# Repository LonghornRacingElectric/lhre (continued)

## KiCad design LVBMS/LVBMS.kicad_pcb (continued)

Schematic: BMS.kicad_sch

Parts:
C26, C27: 10n; C_0603_1608Metric_Pad1.08x0.95mm_HandSolder; Mouser # 581-KAM05AR71E103KH; JLCPCB # C1589
C28, C29, C30: 1u; C_0603_1608Metric_Pad1.08x0.95mm_HandSolder; Mouser # 187-CL10A105KB8NNNC; JLCPCB # C15849
D18: APT1608LZGCK; LED_0603_1608Metric_Pad1.05x0.95mm_HandSolder; Mouser # 604-APT1608LZGCK; JLCPCB # C5246833
FB1: GZ1608D601TF; L_0603_1608Metric_Pad1.05x0.95mm_HandSolder; Mouser # 81-BLM18KN601EH1D; JLCPCB Part Number C1002
Q1: NSS1C201MZ4T3G; SOT-223-3_TabPin2; Mouser # 863-NSS1C201MZ4T1G; JLCPCB # C69714
R33, R34, R35, R37, R38, R45: 1k; R_0603_1608Metric_Pad0.98x0.95mm_HandSolder; Mouser # 71-CRCW0603-1.0K-E3; JLCPCB # C21190
R39: 10; R_1206_3216Metric_Pad1.30x1.75mm_HandSolder; Mouser # 660-SG73P2BTTD8R2J; JLCPCB # C3008858
R43, R69: 1k; R_0603_1608Metric_Pad0.98x0.95mm_HandSolder; Mouser Part Number 603-RT0603FRE071KL
U5: ADBMS6830B; adbms6830_lqfp80; Mouser # 584-ADBMS6830BCSWZ; JLCPCB # C9900046081

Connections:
+3V3: R45.1; also elsewhere on the board
/BMS/CSB: U5.58 (IMA); also elsewhere on the board
/BMS/Cell Voltage Sensing/C1: U5.57 (C1); also elsewhere on the board
/BMS/Cell Voltage Sensing/C2: U5.51 (C2); also elsewhere on the board
/BMS/Cell Voltage Sensing/C2:1: U5.54 (C2:1); also elsewhere on the board
/BMS/Cell Voltage Sensing/C3: U5.50 (C3); also elsewhere on the board
/BMS/Cell Voltage Sensing/C4: U5.44 (C4); also elsewhere on the board
/BMS/Cell Voltage Sensing/C4:3: U5.47 (C4:3); also elsewhere on the board
/BMS/Cell Voltage Sensing/C5: U5.43 (C5); also elsewhere on the board
/BMS/Cell Voltage Sensing/C6: U5.37 (C6); also elsewhere on the board
/BMS/Cell Voltage Sensing/C6:5: U5.40 (C6:5); also elsewhere on the board
/BMS/Cell Voltage Sensing/C7: U5.36 (C7); also elsewhere on the board
/BMS/Cell Voltage Sensing/C8-16: R34.2, U5.2 (C16), U5.3 (S16N), U5.4 (S16P), U5.5 (C16:15), U5.6 (S15N), U5.7 (S15P), U5.8 (C15), U5.9 (C14), U5.10 (S14N), U5.11 (S14P), U5.12 (C14:13), U5.13 (S13N), U5.14 (S13P), U5.15 (C13), U5.16 (C12), U5.17 (S12N), U5.18 (S12P), U5.19 (C12:11), U5.20 (S11N), U5.21 (S11P), U5.22 (C11), U5.23 (C10), U5.24 (S10N), U5.25 (S10P), U5.26 (C10:9), U5.27 (S9N), U5.28 (S9P), U5.29 (C9), U5.30 (C8), U5.31 (S8N), U5.32 (S8P); also elsewhere on the board
/BMS/Cell Voltage Sensing/C8:7: U5.33 (C8:7); also elsewhere on the board
/BMS/Cell Voltage Sensing/S1N: U5.55 (S1N); also elsewhere on the board
/BMS/Cell Voltage Sensing/S1P: U5.56 (S1P); also elsewhere on the board
/BMS/Cell Voltage Sensing/S2N: U5.52 (S2N); also elsewhere on the board
/BMS/Cell Voltage Sensing/S2P: U5.53 (S2P); also elsewhere on the board
/BMS/Cell Voltage Sensing/S3N: U5.48 (S3N); also elsewhere on the board
/BMS/Cell Voltage Sensing/S3P: U5.49 (S3P); also elsewhere on the board
/BMS/Cell Voltage Sensing/S4N: U5.45 (S4N); also elsewhere on the board
/BMS/Cell Voltage Sensing/S4P: U5.46 (S4P); also elsewhere on the board
/BMS/Cell Voltage Sensing/S5N: U5.41 (S5N); also elsewhere on the board
/BMS/Cell Voltage Sensing/S5P: U5.42 (S5P); also elsewhere on the board
/BMS/Cell Voltage Sensing/S6N: U5.38 (S6N); also elsewhere on the board
/BMS/Cell Voltage Sensing/S6P: U5.39 (S6P); also elsewhere on the board
/BMS/Cell Voltage Sensing/S7N: U5.34 (S7N); also elsewhere on the board
/BMS/Cell Voltage Sensing/S7P: U5.35 (S7P); also elsewhere on the board
/BMS/DRIVE: C27.1, R39.2, U5.65 (DRIVE)
/BMS/SCK: U5.59 (IPA); also elsewhere on the board
/BMS/SDI: U5.61 (NC); also elsewhere on the board
/BMS/SDO: R45.2, U5.64 (NC); also elsewhere on the board
/BMS/Temperature Sensing/T1: U5.79 (GPIO2); also elsewhere on the board
/BMS/Temperature Sensing/T2: U5.78 (GPIO3); also elsewhere on the board
/BMS/Temperature Sensing/T3: U5.77 (GPIO4); also elsewhere on the board
/BMS/V+: R33.1, R34.1, R35.1, R37.1, R38.1; also elsewhere on the board
/BMS/V_{REG}: C30.1, FB1.1, R69.1, U5.69 (V_{REG})
GND: C26.2, C27.2, C28.2, C29.2, C30.2, U5.60 (ISOMD), U5.67 (V-), U5.81 (EP); also elsewhere on the board
unnamed: D18.2 (A), R43.2
unnamed: D18.1 (K), U5.80 (GPIO1)
unnamed: Q1.1 (B), R39.1
unnamed: C26.1, Q1.2 (C), R35.2, R37.2, R38.2
unnamed: FB1.2, Q1.3 (E)
unnamed: R43.1, R69.2
unnamed: R33.2, U5.1 (V+)
unnamed: C29.1, U5.70 (V_{REF1})
V_{REF2}: C28.1, U5.68 (V_{REF2})

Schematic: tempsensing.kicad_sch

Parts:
JP6, JP7, JP8: TH1; PinSocket_1x02_P2.54mm_Vertical
R40, R41, R42: 10k; R_0603_1608Metric_Pad0.98x0.95mm_HandSolder; Mouser # 71-CRCW0603-10K-E3; JLCPCB # C25804
TH1, TH2, TH3: 10k; BSB_Thermistor_Pad; Mouser # 954-103AT-4-10228; not fitted

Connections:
+3V3: R40.1, R41.1, R42.1; also elsewhere on the board
/BMS/Temperature Sensing/T1: JP6.2 (B), R42.2, TH1.1; also elsewhere on the board
/BMS/Temperature Sensing/T2: JP7.2 (B), R40.2, TH2.1; also elsewhere on the board
/BMS/Temperature Sensing/T3: JP8.2 (B), R41.2, TH3.1; also elsewhere on the board
GND: JP6.1 (A), JP7.1 (A), JP8.1 (A), TH1.2, TH2.2, TH3.2; also elsewhere on the board

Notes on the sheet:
Temp. Sense

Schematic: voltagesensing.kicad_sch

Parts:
C10, C12, C34, C36, C37, C38: 100n; C_0603_1608Metric_Pad1.08x0.95mm_HandSolder; Mouser # 581-KAM15BR72A104KT; JLCPCB # C14663
C11, C39, C40, C41, C42, C43, C44, C46: 10n; C_0603_1608Metric_Pad1.08x0.95mm_HandSolder; Mouser # 843-0603B103K101NT; JLCPCB # C43253
C35: 100n; C_0603_1608Metric_Pad1.08x0.95mm_HandSolder; Mouser # 581-06031C104K4T2A; JLCPCB # C14663
F4, F5, F11, F12, F13, F14, F15, F16: 1A; Fuse_0603_1608Metric_Pad1.05x0.95mm_HandSolder; Mouser # 504-TR-0603HV1-R; JLCPCB # C136329
R13, R14, R36, R46, R47, R50, R59, R60, R61, R62, R63, R64, R65, R66: 10; R_1206_3216Metric_Pad1.30x1.75mm_HandSolder; Mouser # 660-SG73P2BTTD8R2J; JLCPCB # C3008858
R67, R68: 200; R_0603_1608Metric_Pad0.98x0.95mm_HandSolder; Mouser # 303-0603WAF1000T5E; JLCPCB # C22775
R70, R71, R72, R73, R74, R76, R77, R78, R79: 200; R_0603_1608Metric_Pad0.98x0.95mm_HandSolder; Mouser # 303-0603WAF2000T5E; JLCPCB # C8218
TP5: +20.6V; TestPoint_Keystone_5010-5014_Multipurpose
TP6: +17.1V; TestPoint_Keystone_5010-5014_Multipurpose
TP7: +13.7V; TestPoint_Keystone_5010-5014_Multipurpose
TP8: +10.3V; TestPoint_Keystone_5010-5014_Multipurpose
TP9: +6.9V; TestPoint_Keystone_5010-5014_Multipurpose
TP10: +3.4V; TestPoint_Keystone_5010-5014_Multipurpose
TP11: GND; TestPoint_Keystone_5010-5014_Multipurpose
TP12: +24V; TestPoint_Keystone_5010-5014_Multipurpose

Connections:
+24V: F12.1, TP12.1 (1_1); also elsewhere on the board
/BMS/Cell Voltage Sensing/C1: C11.2, R79.2; also elsewhere on the board
/BMS/Cell Voltage Sensing/C2: C46.1, R77.2; also elsewhere on the board
/BMS/Cell Voltage Sensing/C2:1: C11.1, C46.2, R78.2; also elsewhere on the board
/BMS/Cell Voltage Sensing/C3: C44.2, R76.2; also elsewhere on the board
/BMS/Cell Voltage Sensing/C4: C43.1, R73.2; also elsewhere on the board
/BMS/Cell Voltage Sensing/C4:3: C43.2, C44.1, R74.2; also elsewhere on the board
/BMS/Cell Voltage Sensing/C5: C42.2, R72.2; also elsewhere on the board
/BMS/Cell Voltage Sensing/C6: C41.1, R70.2; also elsewhere on the board
/BMS/Cell Voltage Sensing/C6:5: C41.2, C42.1, R71.2; also elsewhere on the board
/BMS/Cell Voltage Sensing/C7: C40.2, R68.2; also elsewhere on the board
/BMS/Cell Voltage Sensing/C8-16: C39.1; also elsewhere on the board
/BMS/Cell Voltage Sensing/C8:7: C39.2, C40.1, R67.2; also elsewhere on the board
/BMS/Cell Voltage Sensing/S1N: C10.2, R66.2; also elsewhere on the board
/BMS/Cell Voltage Sensing/S1P: C10.1, R65.2; also elsewhere on the board
/BMS/Cell Voltage Sensing/S2N: C12.2, R14.2; also elsewhere on the board
/BMS/Cell Voltage Sensing/S2P: C12.1, R13.2; also elsewhere on the board
/BMS/Cell Voltage Sensing/S3N: C38.2, R64.2; also elsewhere on the board
/BMS/Cell Voltage Sensing/S3P: C38.1, R63.2; also elsewhere on the board
/BMS/Cell Voltage Sensing/S4N: C37.2, R62.2; also elsewhere on the board
/BMS/Cell Voltage Sensing/S4P: C37.1, R61.2; also elsewhere on the board
/BMS/Cell Voltage Sensing/S5N: C36.2, R60.2; also elsewhere on the board
/BMS/Cell Voltage Sensing/S5P: C36.1, R59.2; also elsewhere on the board
/BMS/Cell Voltage Sensing/S6N: C35.2, R50.2; also elsewhere on the board
/BMS/Cell Voltage Sensing/S6P: C35.1, R47.2; also elsewhere on the board
/BMS/Cell Voltage Sensing/S7N: C34.2, R46.2; also elsewhere on the board
/BMS/Cell Voltage Sensing/S7P: C34.1, R36.2; also elsewhere on the board
/BMS/V+: F12.2, R36.1, R67.1; also elsewhere on the board
GND: F4.1, TP11.1 (1_1); also elsewhere on the board
unnamed: F4.2, R66.1, R79.1
unnamed: F5.1, TP10.1 (1_1)
unnamed: F5.2, R14.1, R65.1, R78.1
unnamed: F11.1, TP5.1 (1_1)
unnamed: F11.2, R46.1, R47.1, R68.1, R70.1
unnamed: F13.1, TP6.1 (1_1)
unnamed: F13.2, R50.1, R59.1, R71.1
unnamed: F14.1, TP7.1 (1_1)
unnamed: F14.2, R60.1, R61.1, R72.1, R73.1
unnamed: F15.1, TP8.1 (1_1)
unnamed: F15.2, R62.1, R63.1, R74.1
unnamed: F16.1, TP9.1 (1_1)
unnamed: F16.2, R13.1, R64.1, R76.1, R77.1

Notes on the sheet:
Voltage Sense

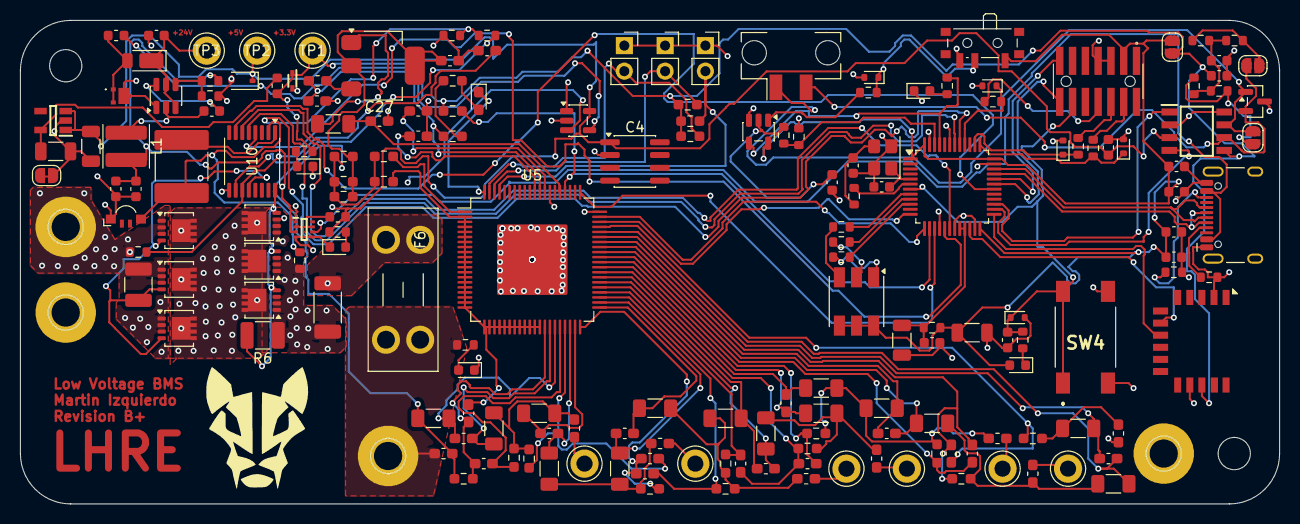
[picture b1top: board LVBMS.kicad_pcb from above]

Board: 4 copper layers, 125.0 x 48.0 mm, 188 parts (0 on the bottom side), 130 nets.

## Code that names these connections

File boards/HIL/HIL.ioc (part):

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Mcu.Name=STM32G474C(B-C-E)Tx
Mcu.Package=LQFP48
Mcu.UserName=STM32G474CETx
PA0.GPIOParameters=PinState,GPIO_Label
PA0.GPIO_Label=LED_G
PA0.PinState=GPIO_PIN_SET
PA0.Signal=GPIO_Output
PA1.GPIOParameters=PinState,GPIO_Label
PA1.GPIO_Label=LED_R
PA1.PinState=GPIO_PIN_SET
PA1.Signal=GPIO_Output
PA10.Mode=Asynchronous
PA10.Signal=USART1_RX
PA13.Mode=Trace_Asynchronous_SW
PA13.Signal=SYS_JTMS-SWDIO
PA14.Mode=Trace_Asynchronous_SW
PA14.Signal=SYS_JTCK-SWCLK
PA15.Mode=I2C
PA15.Signal=I2C1_SCL
PA2.GPIOParameters=PinState,GPIO_Label
PA2.GPIO_Label=LED_B
PA2.PinState=GPIO_PIN_SET
PA2.Signal=GPIO_Output
PA3.GPIOParameters=GPIO_Label
PA3.GPIO_Label=GPIO1
PA3.Signal=GPIO_Output
PA4.GPIOParameters=GPIO_Label,GPIO_ModeDefaultEXTI
PA4.GPIO_Label=SHDN_IN1
PA4.GPIO_ModeDefaultEXTI=GPIO_MODE_IT_RISING_FALLING
PA4.Signal=GPXTI4
PA5.GPIOParameters=GPIO_Label,GPIO_ModeDefaultEXTI
PA5.GPIO_Label=SHDN_IN2
PA5.GPIO_ModeDefaultEXTI=GPIO_MODE_IT_RISING_FALLING
PA5.Signal=GPXTI5
PA6.GPIOParameters=GPIO_Label,GPIO_ModeDefaultEXTI
PA6.GPIO_Label=SHDN_IN3
PA6.GPIO_ModeDefaultEXTI=GPIO_MODE_IT_RISING_FALLING
PA6.Signal=GPXTI6
PA7.GPIOParameters=GPIO_Label
PA7.GPIO_Label=GPIO2
PA7.Signal=GPIO_Output
PA8.Mode=FDCAN_Activate
PA8.Signal=FDCAN3_RX
PA9.Mode=Asynchronous
PA9.Signal=USART1_TX
PB0.GPIOParameters=GPIO_Label
PB0.GPIO_Label=SHDN_CTRL1
PB0.Signal=GPIO_Output
PB1.GPIOParameters=GPIO_Label
PB1.GPIO_Label=SHDN_CTRL2
PB1.Signal=GPIO_Output
PB10.GPIOParameters=GPIO_Label,GPIO_ModeDefaultEXTI
PB10.GPIO_Label=SHDN_IN4
PB10.GPIO_ModeDefaultEXTI=GPIO_MODE_IT_RISING_FALLING
PB10.Signal=GPXTI10
PB11.GPIOParameters=GPIO_Label
PB11.GPIO_Label=SHDN_READBACK1
PB11.Mode=IN14-Single-Ended
PB11.Signal=ADC1_IN14
PB12.GPIOParameters=GPIO_Label
PB12.GPIO_Label=SHDN_READBACK2
PB12.Mode=IN11-Single-Ended
PB12.Signal=ADC1_IN11
PB13.GPIOParameters=GPIO_Label
PB13.GPIO_Label=PWM_OUT
PB13.Mode=PWM Generation1 CH1N
PB13.Signal=TIM1_CH1N
PB14.GPIOParameters=PinState,GPIO_Label
PB14.GPIO_Label=LDAC1
PB14.PinState=GPIO_PIN_SET
PB14.Signal=GPIO_Output
PB15.GPIOParameters=PinState,GPIO_Label
PB15.GPIO_Label=LDAC2
PB15.PinState=GPIO_PIN_SET
PB15.Signal=GPIO_Output
PB2.GPIOParameters=GPIO_Label
PB2.GPIO_Label=GPIO3
PB2.Signal=GPIO_Output
PB3.Mode=Trace_Asynchronous_SW
PB3.Signal=SYS_JTDO-SWO
PB4.Mode=FDCAN_Activate
PB4.Signal=FDCAN3_TX
PB5.Mode=FDCAN_Activate
PB5.Signal=FDCAN2_RX
PB6.Mode=FDCAN_Activate
PB6.Signal=FDCAN2_TX
PB7.Mode=I2C
PB7.Signal=I2C1_SDA
PB9.GPIOParameters=GPIO_Label
PB9.GPIO_Label=BOOT0_TRIG
PB9.Signal=GPIO_Output
PF0-OSC_IN.Mode=HSE-External-Oscillator
PF0-OSC_IN.Signal=RCC_OSC_IN
PF1-OSC_OUT.Mode=HSE-External-Oscillator
PF1-OSC_OUT.Signal=RCC_OSC_OUT
RCC.HSE_VALUE=16000000
RCC.SYSCLKFreq_VALUE=96000000
RCC.SYSCLKSource=RCC_SYSCLKSOURCE_PLLCLK
board=custom
